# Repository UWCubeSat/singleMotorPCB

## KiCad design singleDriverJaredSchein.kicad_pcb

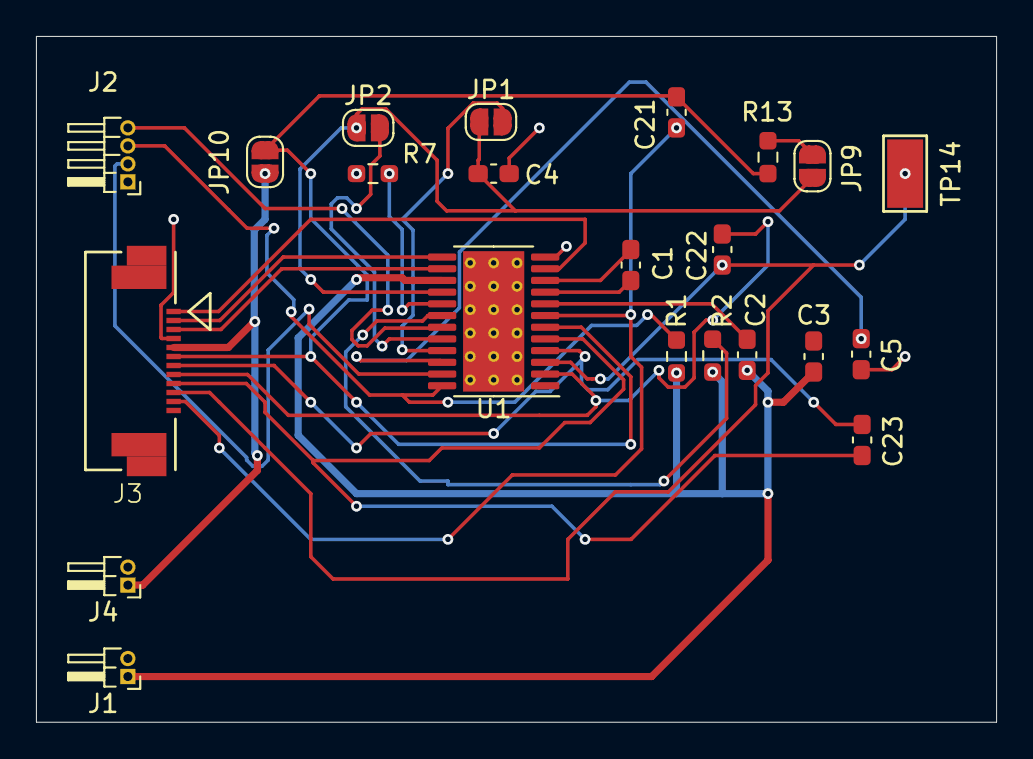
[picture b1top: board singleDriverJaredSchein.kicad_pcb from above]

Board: 2 copper layers, 53.3 x 38.1 mm, 22 parts (0 on the bottom side), 25 nets.

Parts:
C1: 0.1uF X7R; C_0603_1608Metric_Pad1.08x0.95mm_HandSolder
C2, C21, C22, C23: 1uF 16V; C_0603_1608Metric_Pad1.08x0.95mm_HandSolder
C3: 10uF 25V; C_0603_1608Metric_Pad1.08x0.95mm_HandSolder
C4: 2.2uF 10V; C_0603_1608Metric_Pad1.08x0.95mm_HandSolder
C5: 1uF; C_0603_1608Metric_Pad1.08x0.95mm_HandSolder
J1, J4: Conn_01x02_Pin; PinHeader_1x02_P1.00mm_Horizontal
J2: Conn_01x04_Pin; PinHeader_1x04_P1.00mm_Horizontal
J3: conn01x12
JP1, JP2, JP9, JP10: Jumper; SolderJumper-2_P1.3mm_Open_RoundedPad1.0x1.5mm
R1, R2, R13: 3.3k; R_0603_1608Metric_Pad0.98x0.95mm_HandSolder
R7: 24k; R_0603_1608Metric_Pad0.98x0.95mm_HandSolder
TP14: U_HN; TestPoint_Keystone_5019_Minature
U1: DRV10970; HTSSOP-24-1EP_4.4x7.8mm_P0.65mm_EP3.4x7.8mm_Mask2.4x4.68mm_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

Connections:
+5V: J3.5, J4.1, JP10.2 (B)
+12V: C2.1, C3.2, J1.1, R1.1, R2.1, U1.15 (VM)
/FG: J2.3, R1.2, U1.24 (FG)
/FR: J2.2, U1.23 (FR)
/PWM: J2.4, U1.19 (PWM)
/VINT: C4.2, JP1.1 (A), JP2.1 (A), JP9.2 (B), U1.16 (VINT)
GND: C3.1, C4.1, C5.1, J1.2, J2.1, J3.4, J4.2, R7.1, U1.12 (GND), U1.25 (EPAD)
unnamed: C22.2, J3.8, U1.2 (U_HP)
unnamed: C22.1, J3.10, TP14.1, U1.3 (U_HN)
unnamed: C23.2, J3.7, U1.4 (V_HP)
unnamed: C23.1, J3.9, U1.5 (V_HN)
unnamed: C21.2, J3.6, JP10.1 (A), R13.2, U1.6 (W_HP)
unnamed: C21.1, J3.11, U1.7 (W_HN)
unnamed: J3.3, U1.14 (U)
unnamed: J3.2, U1.13 (V)
unnamed: J3.1, U1.11 (W)
unnamed: JP1.2 (B), U1.21 (BRKMOD)
unnamed: JP2.2 (B), U1.20 (CMTMOD)
unnamed: JP9.1 (A), R13.1
unnamed: C1.1, U1.10 (CPN)
unnamed: C1.2, U1.9 (CPP)
unnamed: R7.2, U1.17 (CS)
unnamed: R2.2, U1.18 (RD)
unnamed: C5.2, U1.22 (RETRY)
unnamed: C2.2, U1.8 (VCP)
